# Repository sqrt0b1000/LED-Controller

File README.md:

# LED Controller: Schaltplatine für WLED

## Disclaimer

Using this software and hardware is the users responsibility as it is not bug free.
Therefore contributors of this repo are not reliable for anything
including but not limited to spontaneous combustion of the entire led strip, the house and the inevitable heat death of the universe.

Also see: [LICENSE](./LICENSE)

## Features

- 3 PWM Ausgänge zum Steuern von 12 V RGB Kanälen
- Steuerung durch WIFI (einwahl in WLAN möglich oder Erstellen eines eigenen Accesspoints)
- 6 weitere GPIO Pins, z.B. für weitere Buttons,…
- RX/TX Verbindungen (Flashen des ESP32)

## Zusätzliche Features

- 8 PWM Ausgänge als Datenleitungen für individuell addressierbare LEDs
  - Signal auf 5 V
  - Mögliche LED - Strips (nicht vollständig)
    - WS2812
    - WS2805

## Pins

| ESP Pin Name | Board Output | Usage |
| ---------------:| ---------------:| ---------------:|
| TXD0 | J  7 | GPIO1, U0TXD, CLK_OUT3, EMAC_RXD2 |
| RXD0 | J  8 | GPIO3, U0RXD, CLK_OUT2 |
| IO 18 | LED-Out | MOSFET Transisotr 12 V |
| IO 19 | LED-Out | MOSFET Transisotr 12 V |
| IO 21 | LED-Out | MOSFET Transisotr 12 V |
| IO  2 | J  5 | MOSFET Transistor  5 V |
| IO 15 | J 11 | MOSFET Transistor  5 V |
| IO 13 | J 12 | MOSFET Transistor  5 V |
| IO 12 | J 13 | MOSFET Transistor  5 V |
| IO 14 | J 14 | MOSFET Transistor  5 V |
| IO 27 | J 15 | MOSFET Transistor  5 V |
| IO 26 | J 16 | MOSFET Transistor  5 V |
| IO 25 | J 17 | MOSFET Transistor  5 V |
| SENSOR_VN | J 4 | GPIO39, ADC1_CH3, RTC_GPIO3 |
| SENSOR_VP | J 5 | GPIO36, ADC1_CH0, RTC_GPIO0 |
| - | J  9 | Ground |
|  - | J 10 | Power 3.3 V |
|  - | J  2| Power  12 V |

Für mehr Details siehe das Datasheet des Controllers: [Datasheet](./Datasheets/ESP32/esp32-wroom-32_datasheet_en.pdf))

## Probleme mit v01

- sehr hohe Last auf Ground
  - diese Leiterbahnen sollten breiter und idealerweise kürzer sein
- zentraler Ground von ESP32 nicht wirklich lötbar
  - hier richtige Löcher, damit man auf der Rückseite mit dem Lötkolben auch hinkommt
- Pads von Spanungsregulierer anpassen
  - verhindern von Verbindungen von 12 V und 3.3 V beim Löten
- anpassen der Löchergrößen um Pins einfacher durchsteckbar zu machen
- fehlender Pin für 5 V
- Verbindung von Dir mit 5 V, damit Richtung stimmt
- mehr Pins für GND and 12 V
- weitere Pins für freie IO Ports
- Benennung und Beschriftung der Pins
- verbinde benutzbare Pins, nicht (nicht 17-22, da diese intern vom ESP32 benutzt werden, und nicht verbunden sind)

## Flashen des ESP32

(Nur für einen neuen Controller notwendig, alle weiteren Updates können OTA erfolgen)

Verbinden von RX/TX mit Flipper, oder anderem Board.
Flipper oder alternatives Board als UART-USB-Bridge verwenden.
In WLED folgenden Command ausführen.
Davor den Boot-Button am Controller drücken,
um diesen in den Boot-Modus zu versetzen.

´´´bash
pio run -e esp32dev -t upload
´´´
Nach erfolgreichem Flashen den ESP32 mit dem Reset-Button resetten.

## Links

### WLED

- [WLED-Knowlege base](https://kno.wled.ge)
- [WLED-Github](https://github.com/WLED/WLED)
- [WLED-MM](https://github.com/MoonModules/WLED-MM): More advanced WLED with additional / experimental features

### LED-FX (Audio-Reactive)

- [LED-FX-Github](https://github.com/LedFx/LedFx)
- [LED-FX-Documentation](https://docs.ledfx.app/en/latest/installing.html)

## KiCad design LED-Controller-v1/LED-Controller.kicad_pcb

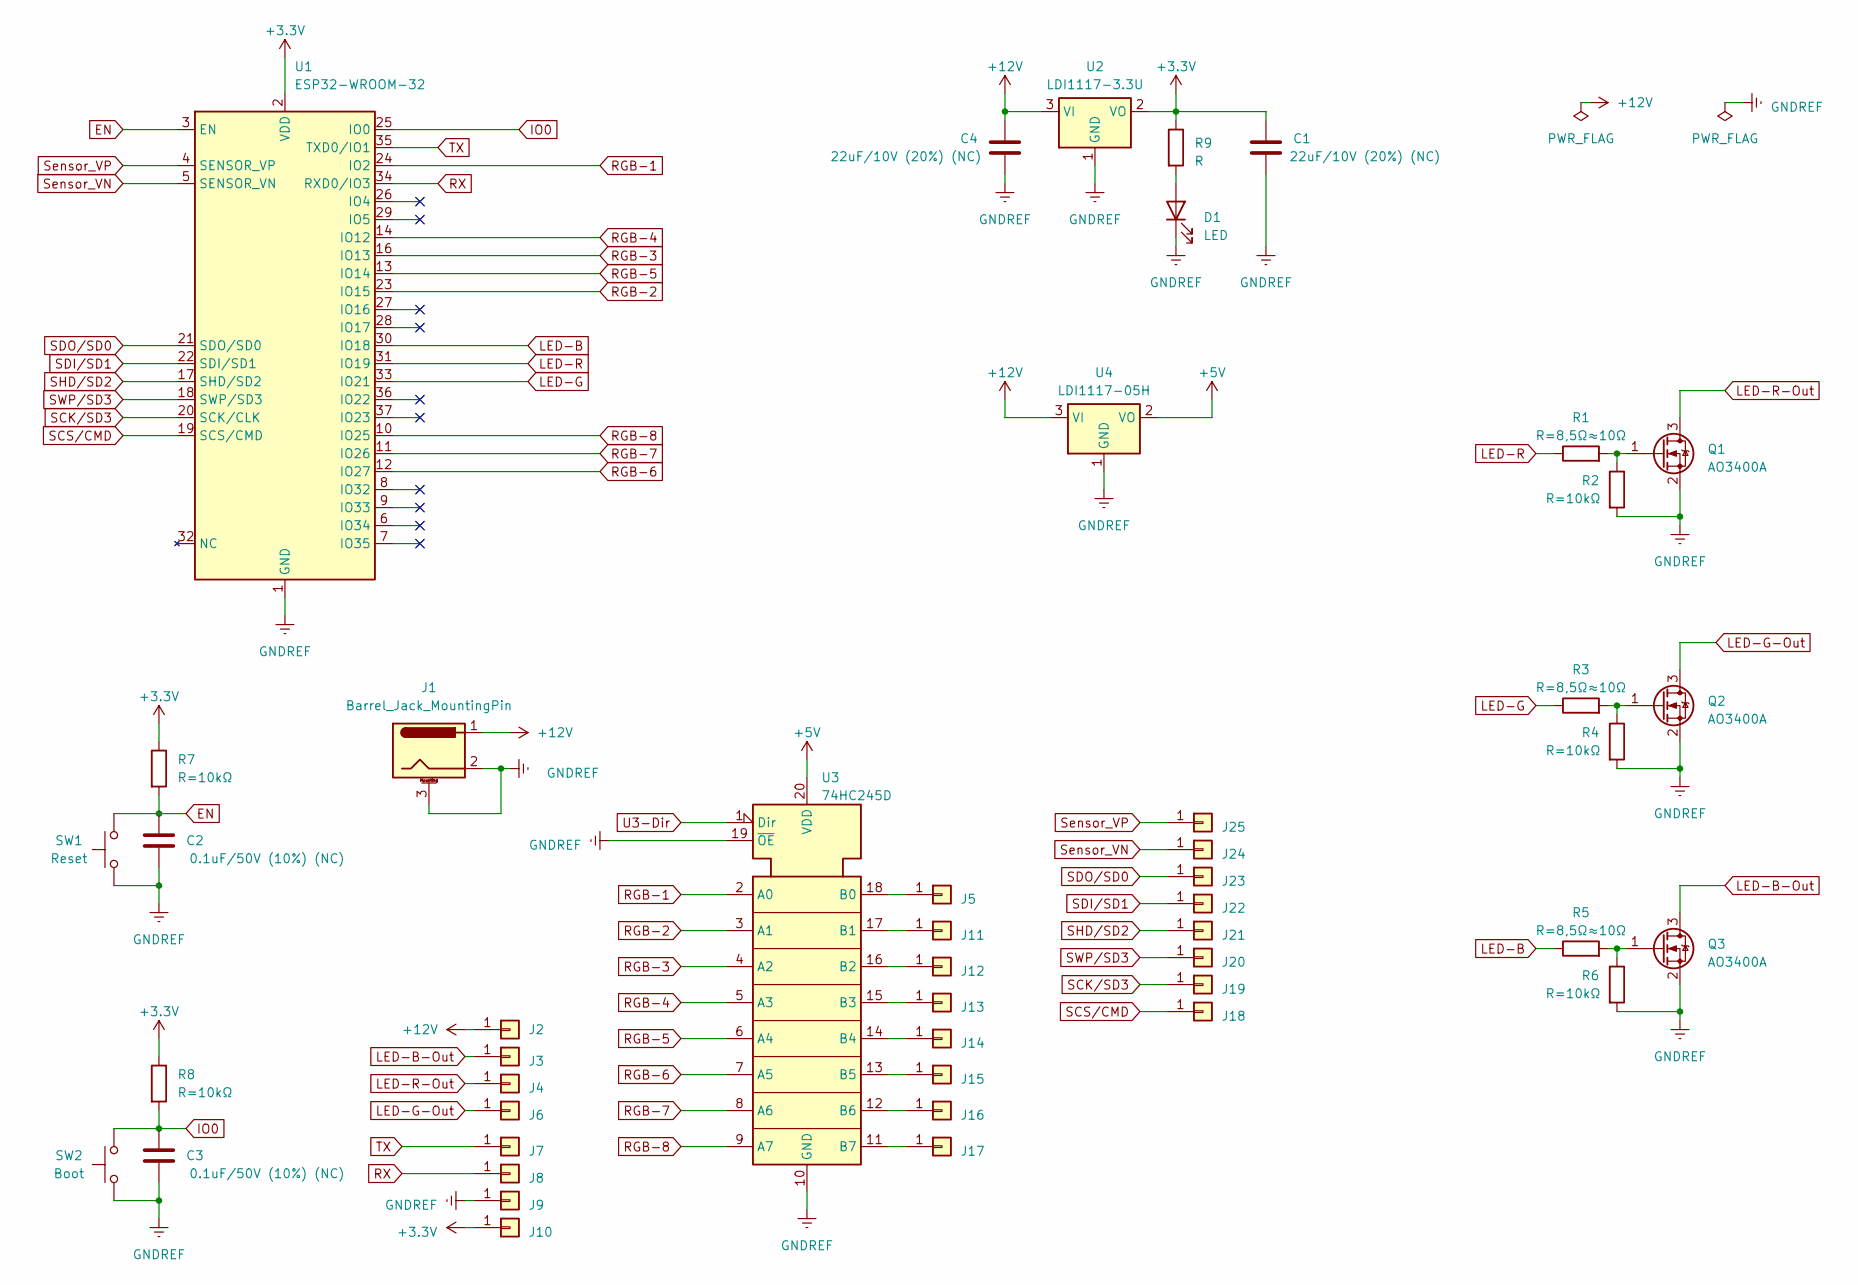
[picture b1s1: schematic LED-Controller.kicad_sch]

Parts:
C1, C4: 22uF/10V (20%) (NC); C_0402_1005Metric_Pad0.74x0.62mm_HandSolder
C2, C3: 0.1uF/50V (10%) (NC); C_0402_1005Metric_Pad0.74x0.62mm_HandSolder
D1: LED; D_0402_1005Metric_Pad0.77x0.64mm_HandSolder
J1: Barrel_Jack_MountingPin; BarrelJack_Horizontal
J2, J3, J4, J6: Conn_01x01; SolderWire-0.1sqmm_1x01_D0.4mm_OD1mm
J5, J7, J8, J9, J10, J11, J12, J13, J14, J15, J16, J17, J18, J19, J20, J21, J22, J23, J24, J25: Conn_01x01; PinHeader_1x01_P1.00mm_Vertical
Q1, Q2, Q3: AO3400A; SOT-23
R1, R3, R5: R=8,5Ω≈10Ω; R_0402_1005Metric_Pad0.72x0.64mm_HandSolder
R2, R4, R6, R7, R8: R=10kΩ; R_0402_1005Metric_Pad0.72x0.64mm_HandSolder
R9: R; R_0402_1005Metric_Pad0.72x0.64mm_HandSolder
SW1: Reset; TACTM-34N-F
SW2: Boot; TACTM-34N-F
U1: ESP32-WROOM-32
U2: LDI1117-3.3U; SOT-89-3_Handsoldering
U3: 74HC245D; SOIC-20W_7.5x12.8mm_P1.27mm
U4: LDI1117-05H; SOT-223-3_TabPin2

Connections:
+3.3V: C1.2, J10.1, R7.1, R8.1, R9.1, U1.2 (VDD), U2.2 (VO)
+5V: U3.20 (VDD), U4.2 (VO)
+12V: C4.2, J1.1, J2.1, U2.3 (VI), U4.3 (VI)
EN: C2.2, R7.2, SW1.2, U1.3 (EN)
GNDREF: C1.1, C2.1, C3.1, C4.1, D1.1 (K), J1.2, J1.3 (MountPin), J9.1, Q1.2 (S), Q2.2 (S), Q3.2 (S), R2.2, R4.2, R6.2, SW1.1, SW2.1, U1.1 (GND), U1.15 (GND), U1.38 (GND), U1.39 (GND), U2.1 (GND), U3.10 (GND), U3.19 (~OE), U4.1 (GND)
IO0: C3.2, R8.2, SW2.2, U1.25 (IO0)
LED-B: R5.1, U1.30 (IO18)
LED-B-Out: J3.1, Q3.3 (D)
LED-G: R3.1, U1.33 (IO21)
LED-G-Out: J6.1, Q2.3 (D)
LED-R: R1.1, U1.31 (IO19)
LED-R-Out: J4.1, Q1.3 (D)
unnamed: D1.2 (A), R9.2
unnamed: J5.1, U3.18 (B0)
unnamed: J11.1, U3.17 (B1)
unnamed: J12.1, U3.16 (B2)
unnamed: J13.1, U3.15 (B3)
unnamed: J14.1, U3.14 (B4)
unnamed: J15.1, U3.13 (B5)
unnamed: J16.1, U3.12 (B6)
unnamed: J17.1, U3.11 (B7)
unnamed: Q1.1 (G), R1.2, R2.1
unnamed: Q2.1 (G), R3.2, R4.1
unnamed: Q3.1 (G), R5.2, R6.1
RGB-1: U1.24 (IO2), U3.2 (A0)
RGB-2: U1.23 (IO15), U3.3 (A1)
RGB-3: U1.16 (IO13), U3.4 (A2)
RGB-4: U1.14 (IO12), U3.5 (A3)
RGB-5: U1.13 (IO14), U3.6 (A4)
RGB-6: U1.12 (IO27), U3.7 (A5)
RGB-7: U1.11 (IO26), U3.8 (A6)
RGB-8: U1.10 (IO25), U3.9 (A7)
RX: J8.1, U1.34 (RXD0/IO3)
SCK/SD3: J19.1, U1.20 (SCK/CLK)
SCS/CMD: J18.1, U1.19 (SCS/CMD)
SDI/SD1: J22.1, U1.22 (SDI/SD1)
SDO/SD0: J23.1, U1.21 (SDO/SD0)
SHD/SD2: J21.1, U1.17 (SHD/SD2)
SWP/SD3: J20.1, U1.18 (SWP/SD3)
Sensor_VN: J24.1, U1.5 (SENSOR_VN)
Sensor_VP: J25.1, U1.4 (SENSOR_VP)
TX: J7.1, U1.35 (TXD0/IO1)
U3-Dir: U3.1 (Dir)

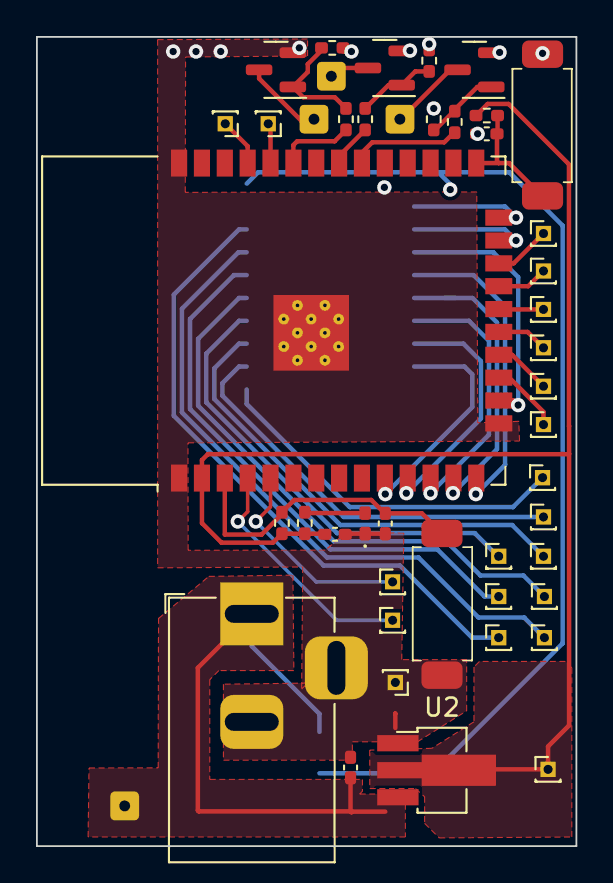
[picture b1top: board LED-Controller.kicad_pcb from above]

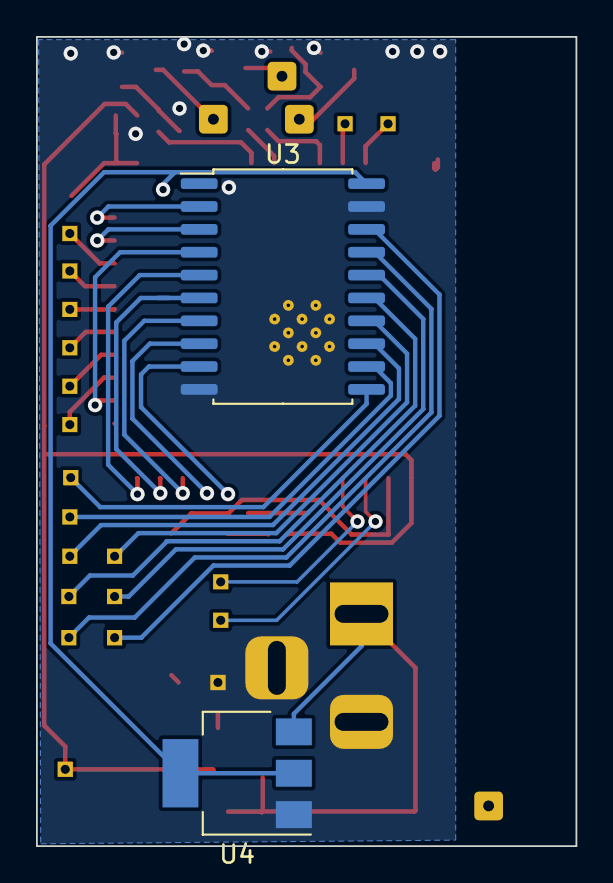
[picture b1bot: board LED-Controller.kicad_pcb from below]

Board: 2 copper layers, 30.0 x 45.0 mm, 48 parts (2 on the bottom side), 42 nets.

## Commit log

2025-04-06 Initial version of Floor PCB
2025-04-06 Adjust minor things in documentation
